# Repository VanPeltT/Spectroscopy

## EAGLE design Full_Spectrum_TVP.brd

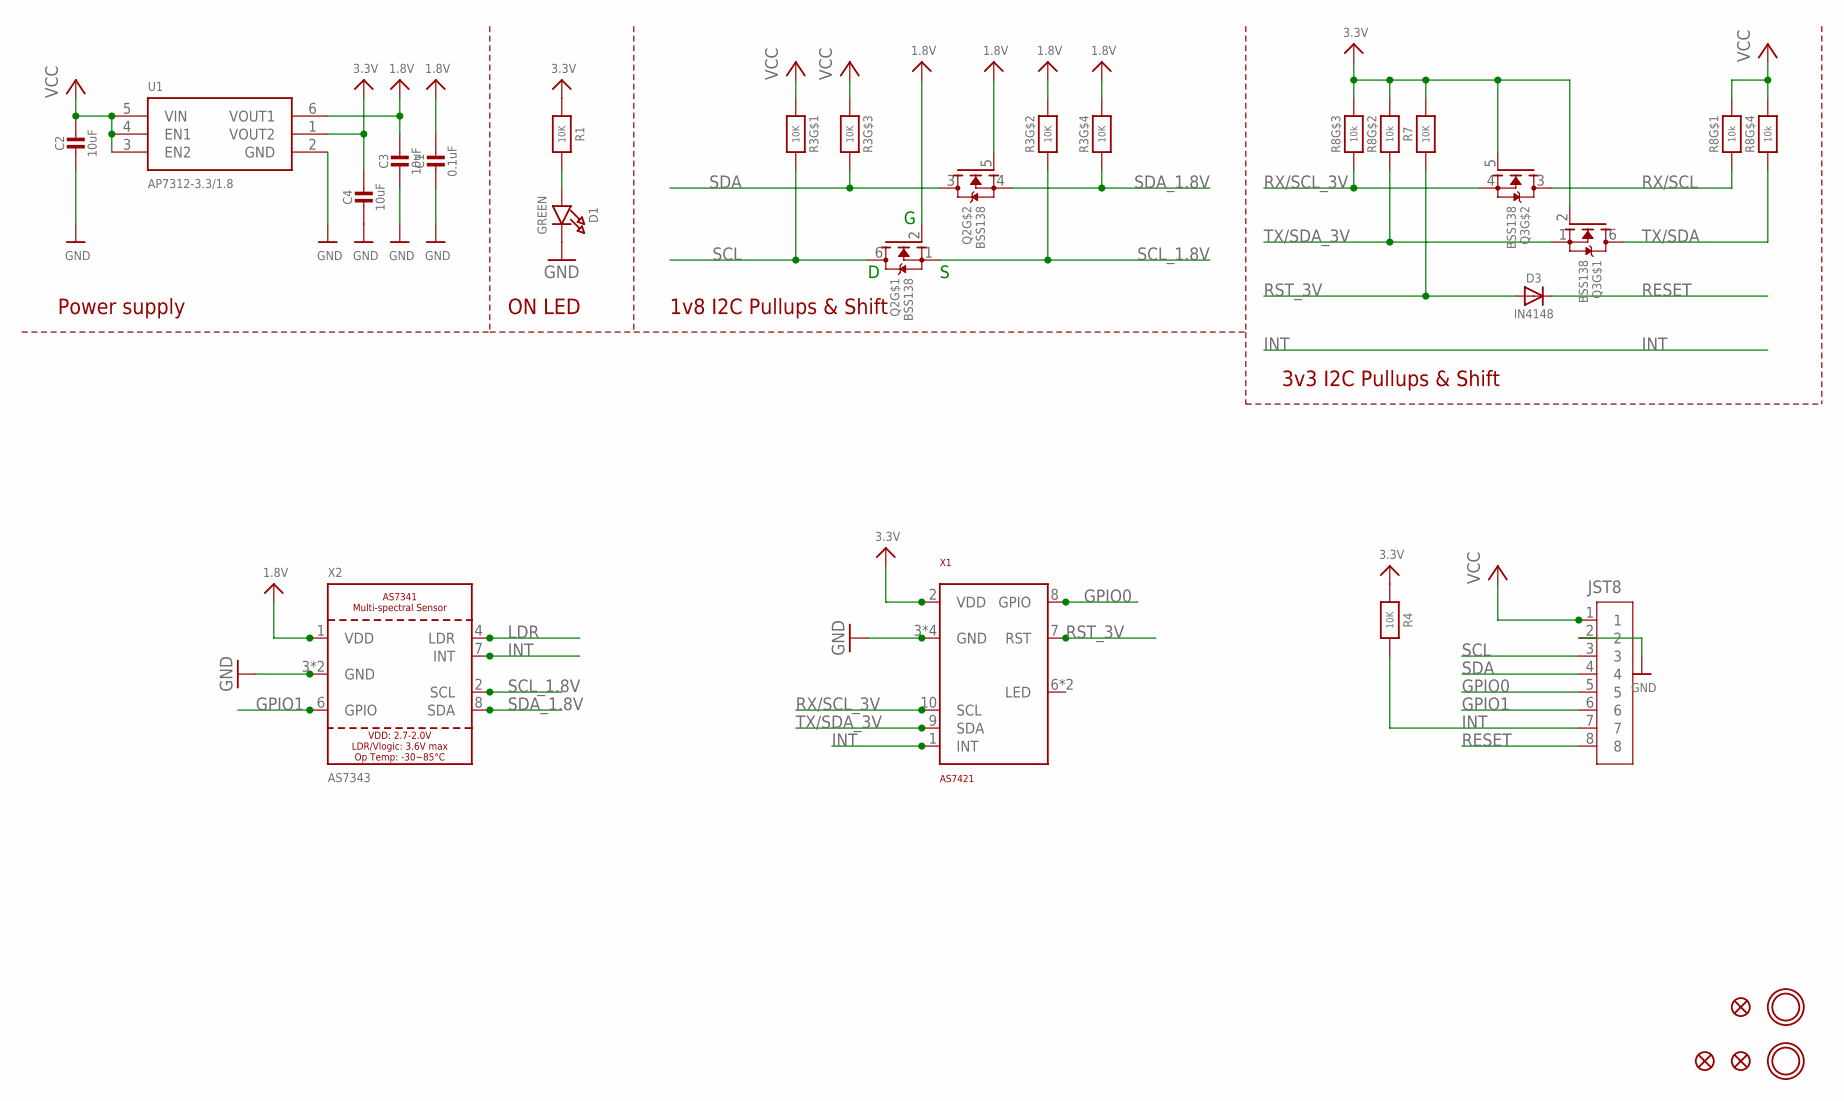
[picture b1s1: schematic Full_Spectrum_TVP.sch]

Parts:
C1: 0.1uF; 0603-NO
C2, C3, C4: 10uF; 0805-NO
D1: GREEN; CHIPLED_0603_NOOUTLINE
D3: IN4148; SOD-323
FID1, FID3, FID4: FIDUCIAL_1MM
Q2, Q3: BSS138; SOT363
R1, R4, R7: 10K; 0603-NO
R3: 10K; RESPACK_4X0603
R8: 10k; RESPACK_4X0603_NO
SV1: JST8-2.0
U1: AP7312-3.3/1.8; SOT23-6
U$1, U$17: MOUNTINGHOLE2.5; MOUNTINGHOLE_2.5_PLATED
X1: AS7421
X2: AS7343; AS7341

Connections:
1.8V: C1.1, C3.1, Q2.2 (G), Q2.5 (G), R3.2 (1), R3.4 (1), U1.6 (VOUT1), X2.1 (VDD)
3.3V: C4.1, Q3.2 (G), Q3.5 (G), R1.1, R4.1, R7.2, R8.6 (2), R8.7 (2), U1.1 (VOUT2), X1.2 (VDD)
GND: C1.2, C2.2, C3.2, C4.2, D1.C, SV1.2, U1.2 (GND), X1.3 (GND), X1.4 (GND), X1.5 (GND), X1.11 (GND), X2.3 (GND), X2.5 (GND)
GPIO0: SV1.5, X1.8 (GPIO)
GPIO1: SV1.6, X2.6 (GPIO)
INT: R4.2, SV1.7, X1.1 (INT), X2.7 (INT)
LDR: X2.4 (LDR)
unnamed: D1.A, R1.2
RESET: D3.C, SV1.8
RST_3V: D3.A, R7.1, X1.7 (RST)
RX/SCL: Q3.3 (D), R8.1
RX/SCL_3V: Q3.4 (S), R8.3 (1), X1.10 (SCL)
SCL: Q2.6 (D), R3.8 (2), SV1.3
SCL_1.8V: Q2.1 (S), R3.7 (2), X2.2 (SCL)
SDA: Q2.3 (D), R3.6 (2), SV1.4
SDA_1.8V: Q2.4 (S), R3.5 (2), X2.8 (SDA)
TX/SDA: Q3.6 (D), R8.4 (1)
TX/SDA_3V: Q3.1 (S), R8.2 (1), X1.9 (SDA)
VCC: C2.1, R3.1, R3.3 (1), R8.5 (2), R8.8 (2), SV1.1, U1.3 (EN2), U1.4 (EN1), U1.5 (VIN)

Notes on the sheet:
1v8 I2C Pullups & Shift
3v3 I2C Pullups & Shift
ON LED
Power supply

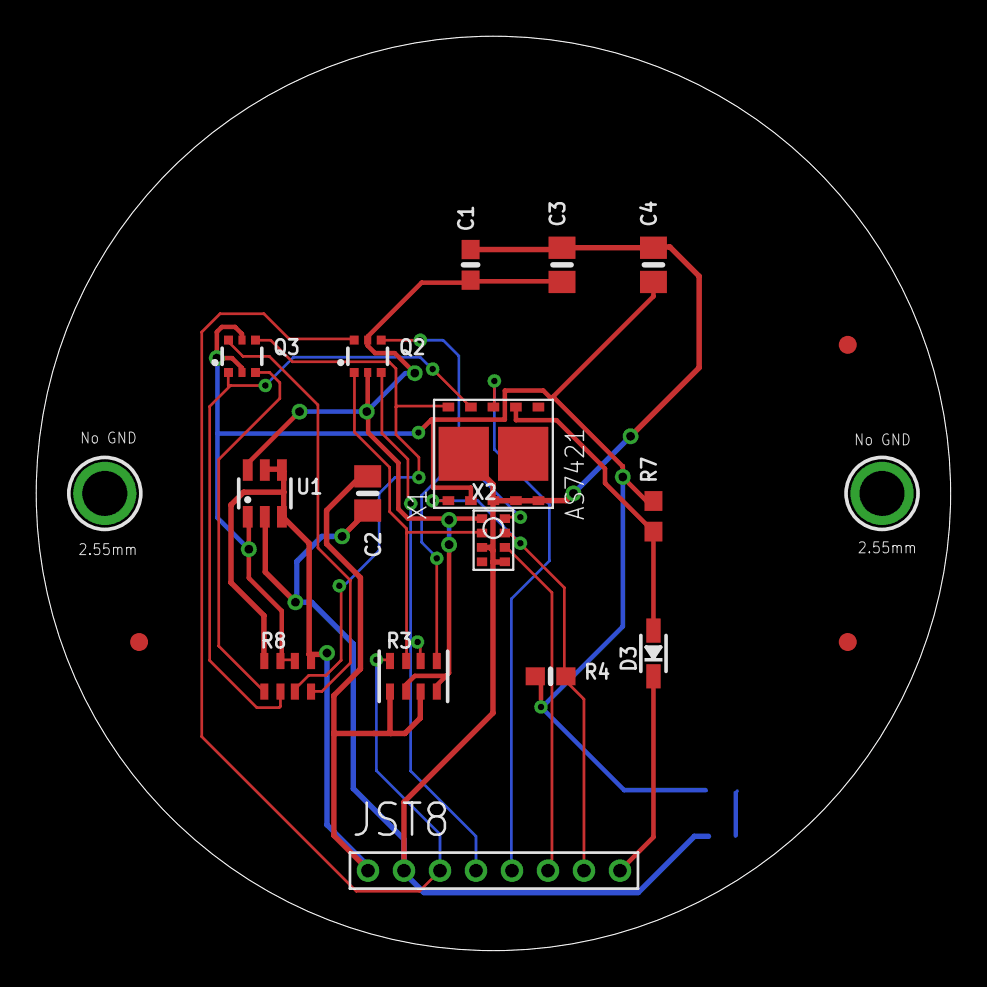
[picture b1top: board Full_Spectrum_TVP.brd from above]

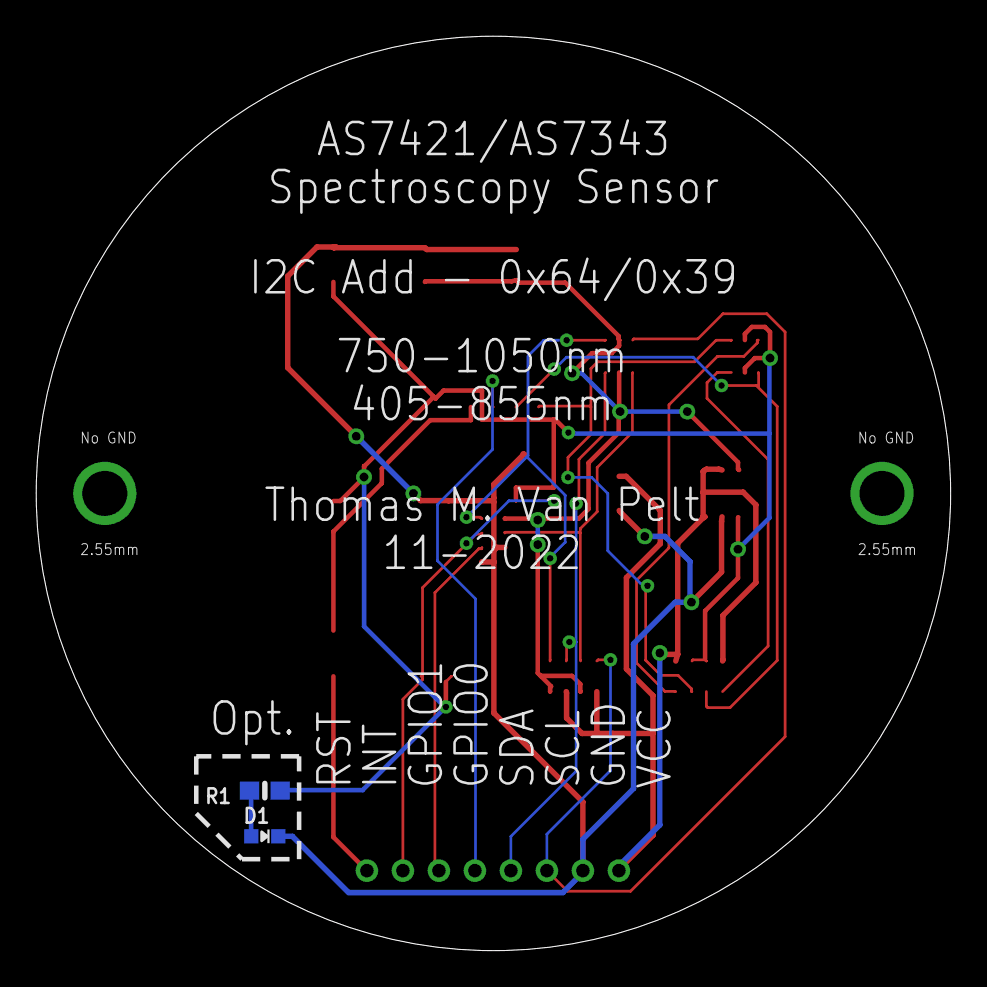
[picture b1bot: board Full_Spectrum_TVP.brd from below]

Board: 2 copper layers, 50.8 x 50.8 mm, 22 parts (2 on the bottom side), 18 nets.

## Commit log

2022-12-07 Add files via upload
    This project is a 2" spectroscopy sensor consisting of a AS7421 and a AS7343. Testing for astronomical purposes. Measurement ranges are 750nm - 1050nm(64 channels) and 405nm - 855nm(14 channels). Som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
2022-12-07 Add files via upload
    Data sheets for the spectrum sensors used in this project.
2022-12-07 Add files via upload
    Bill of materials
2022-12-15 Add files via upload
    Gerber file for board.
2022-12-16 Add files via upload
    Revisions to the traces and spacing. No changes to the schematic.
2023-02-14 Add files via upload
    This code is for an electronic project that uses the Adafruit AS7262 Visible Light Sensor, an I2C interface,
    an ePaper display, and a tactile switch. The code starts by importing the necessary libraries for the project,
    including busio for I2C communication, digitalio for the switch, adafruit_as7262 for the light sensor,
    displayio and terminalio for the display, and numpy and matplotlib for numerical calculations and plotting.
    Next, the code creates an I2C object to communicate with the sensor and initializes the sensor. It also
    initializes the display and creates a switch object. The code then defines the number of readings to store
2023-02-14 Add files via upload
    Using AS7341 sensor, Waveshare 5.65 e-paper display, and Raspberry Pi Pico W.

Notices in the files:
parts and their libraries:
microbuilder: This work is placed in the public domain, and may be freely used for commercial and non-commercial work with the following conditions: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
